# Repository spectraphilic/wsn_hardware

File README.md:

# wsn_hardware
Hardware design for the WSN stations

[Eagle](https://www.autodesk.com/products/eagle/overview) files for sensors and other hardware developed at UiO.

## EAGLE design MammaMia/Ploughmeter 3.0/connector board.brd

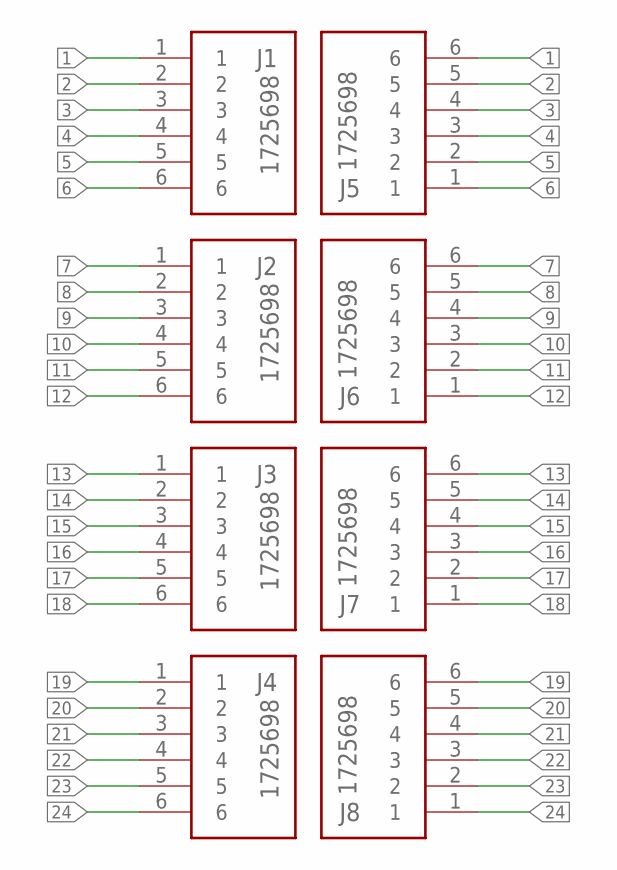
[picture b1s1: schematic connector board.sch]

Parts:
J1, J2, J3, J4, J5, J6, J7, J8: 1725698; SHDR6W90P0X254_1X6_1570X620X85

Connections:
1: J1.1, J5.6
2: J1.2, J5.5
3: J1.3, J5.4
4: J1.4, J5.3
5: J1.5, J5.2
6: J1.6, J5.1
7: J2.1, J6.6
8: J2.2, J6.5
9: J2.3, J6.4
10: J2.4, J6.3
11: J2.5, J6.2
12: J2.6, J6.1
13: J3.1, J7.6
14: J3.2, J7.5
15: J3.3, J7.4
16: J3.4, J7.3
17: J3.5, J7.2
18: J3.6, J7.1
19: J4.1, J8.6
20: J4.2, J8.5
21: J4.3, J8.4
22: J4.4, J8.3
23: J4.5, J8.2
24: J4.6, J8.1

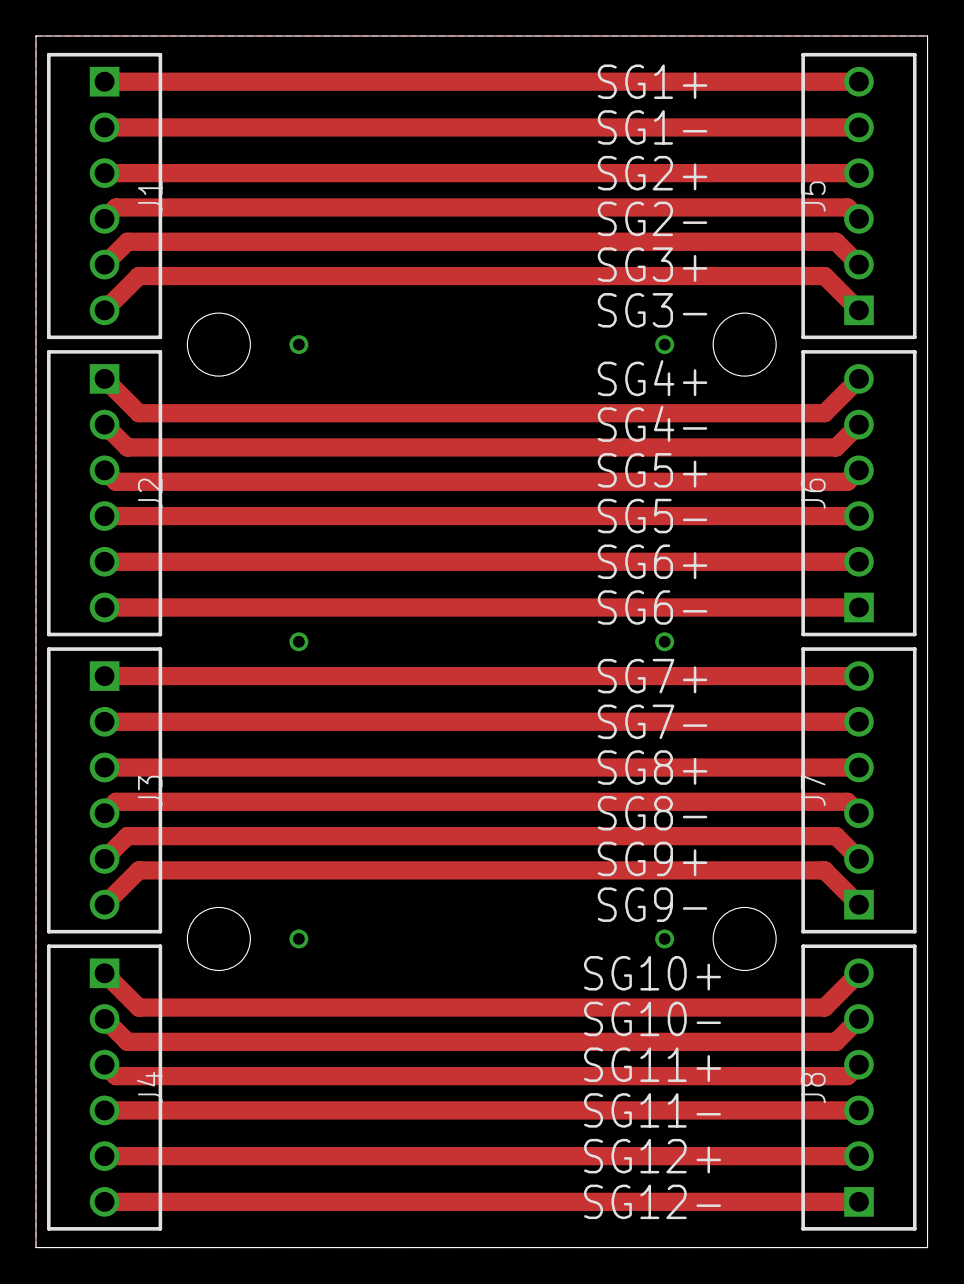
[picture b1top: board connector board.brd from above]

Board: 2 copper layers, 49.5 x 67.3 mm, 8 parts (0 on the bottom side), 24 nets.

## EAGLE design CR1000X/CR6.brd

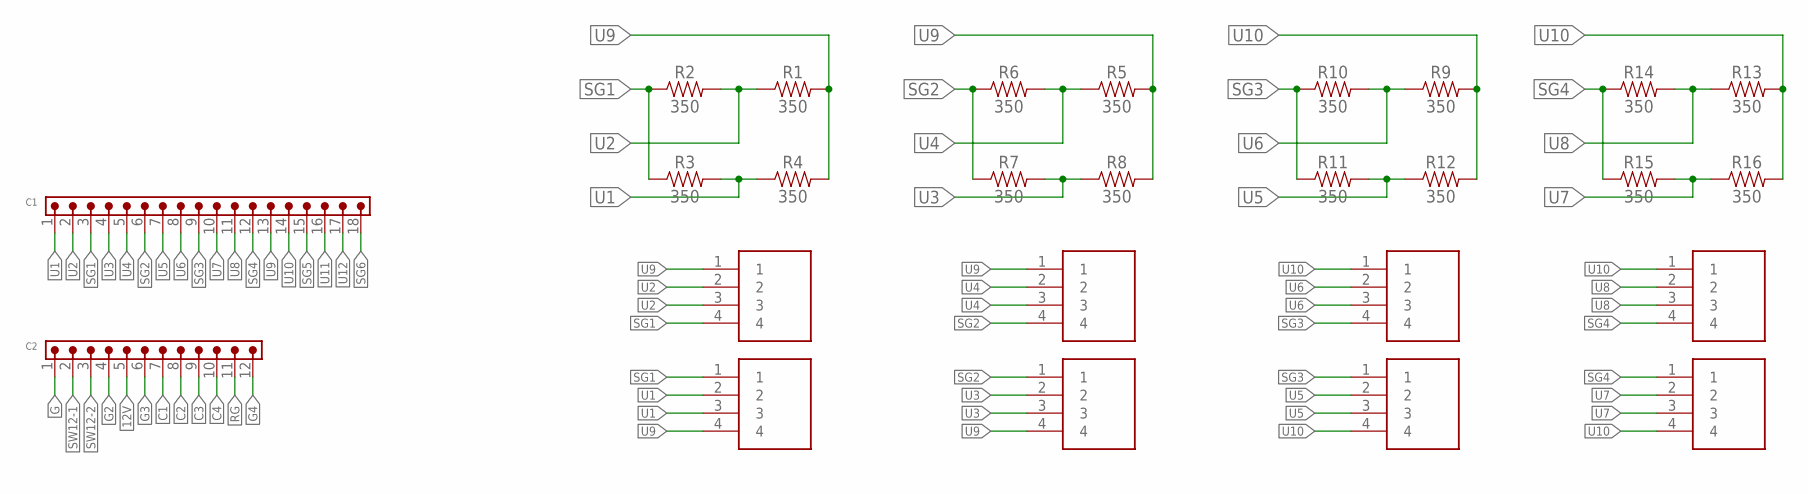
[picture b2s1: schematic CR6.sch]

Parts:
C1: WURTH_CONNECTORS_WR-TBL-PLUGGABLE-CONNECTOR_69131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; WURTH_CONNECTORS_WR-TBL-PLUGGABLE-CONNECTOR_691311500018
C2: WURTH_CONNECTORS_WR-TBL-PLUGGABLE-CONNECTOR_69131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; WURTH_CONNECTORS_WR-TBL-PLUGGABLE-CONNECTOR_691311500012
J1, J2, J5, J6, J9, J10, J13, J14: 1725672; 1725672-4-2.54
R1, R2, R3, R4, R5, R6, R7, R8, R9, R10, R11, R12, R13, R14, R15, R16: 350; AXIAL-0.3

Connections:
12V: C2.5
C1: C2.7
C2: C2.8
C3: C2.9
C4: C2.10
G: C2.1
G2: C2.4
G3: C2.6
G4: C2.12
RG: C2.11
SG1: C1.3, J1.4, J2.1, R2.P$1 (1), R3.P$1 (1)
SG2: C1.6, J5.4, J6.1, R6.P$1 (1), R7.P$1 (1)
SG3: C1.9, J9.4, J10.1, R10.P$1 (1), R11.P$1 (1)
SG4: C1.12, J13.4, J14.1, R14.P$1 (1), R15.P$1 (1)
SG5: C1.15
SG6: C1.18
SW12-1: C2.2
SW12-2: C2.3
U1: C1.1, J2.2, J2.3, R3.P$2 (2), R4.P$1 (1)
U2: C1.2, J1.2, J1.3, R1.P$1 (1), R2.P$2 (2)
U3: C1.4, J6.2, J6.3, R7.P$2 (2), R8.P$1 (1)
U4: C1.5, J5.2, J5.3, R5.P$1 (1), R6.P$2 (2)
U5: C1.7, J10.2, J10.3, R11.P$2 (2), R12.P$1 (1)
U6: C1.8, J9.2, J9.3, R9.P$1 (1), R10.P$2 (2)
U7: C1.10, J14.2, J14.3, R15.P$2 (2), R16.P$1 (1)
U8: C1.11, J13.2, J13.3, R13.P$1 (1), R14.P$2 (2)
U9: C1.13, J1.1, J2.4, J5.1, J6.4, R1.P$2 (2), R4.P$2 (2), R5.P$2 (2), R8.P$2 (2)
U10: C1.14, J9.1, J10.4, J13.1, J14.4, R9.P$2 (2), R12.P$2 (2), R13.P$2 (2), R16.P$2 (2)
U11: C1.16
U12: C1.17

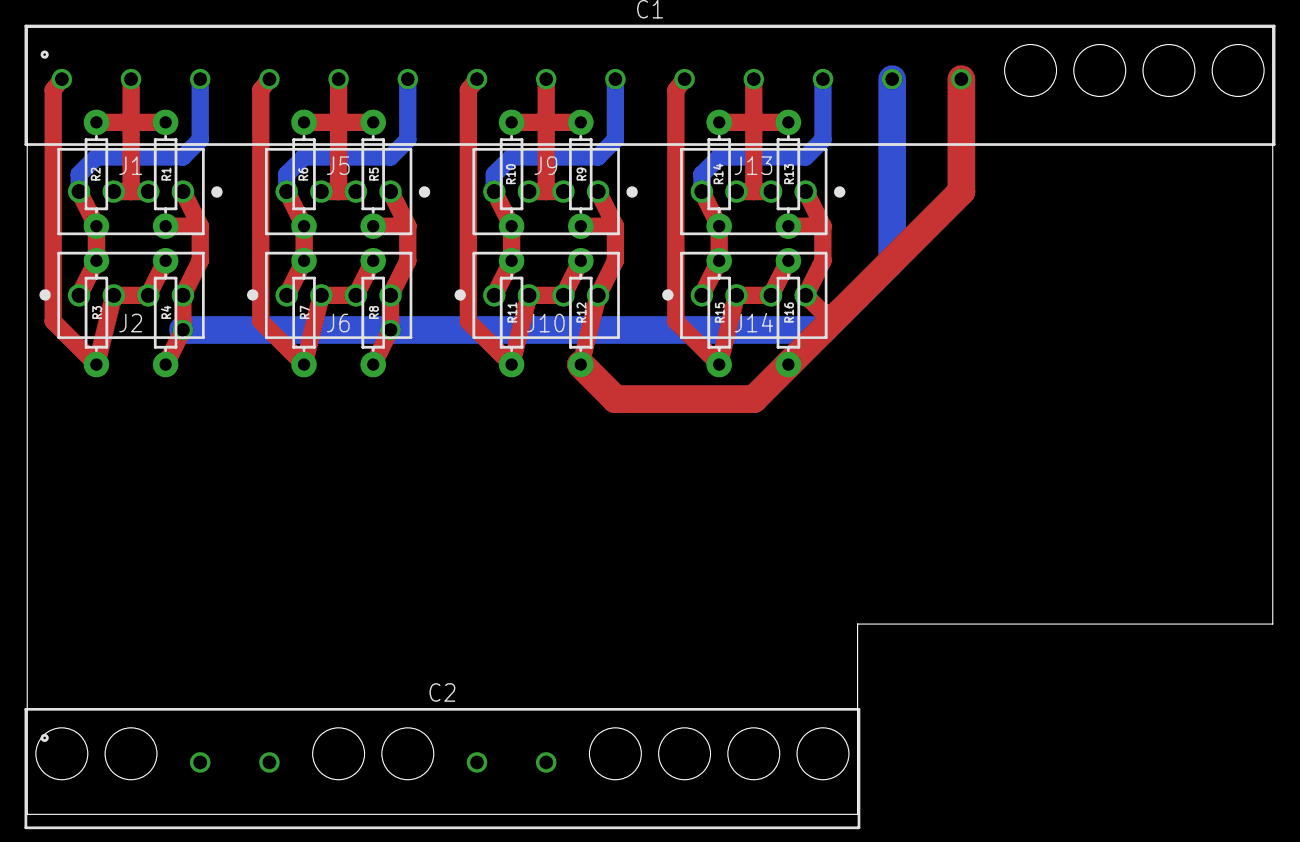
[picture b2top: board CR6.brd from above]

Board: 2 copper layers, 91.4 x 57.8 mm, 26 parts (0 on the bottom side), 14 nets.

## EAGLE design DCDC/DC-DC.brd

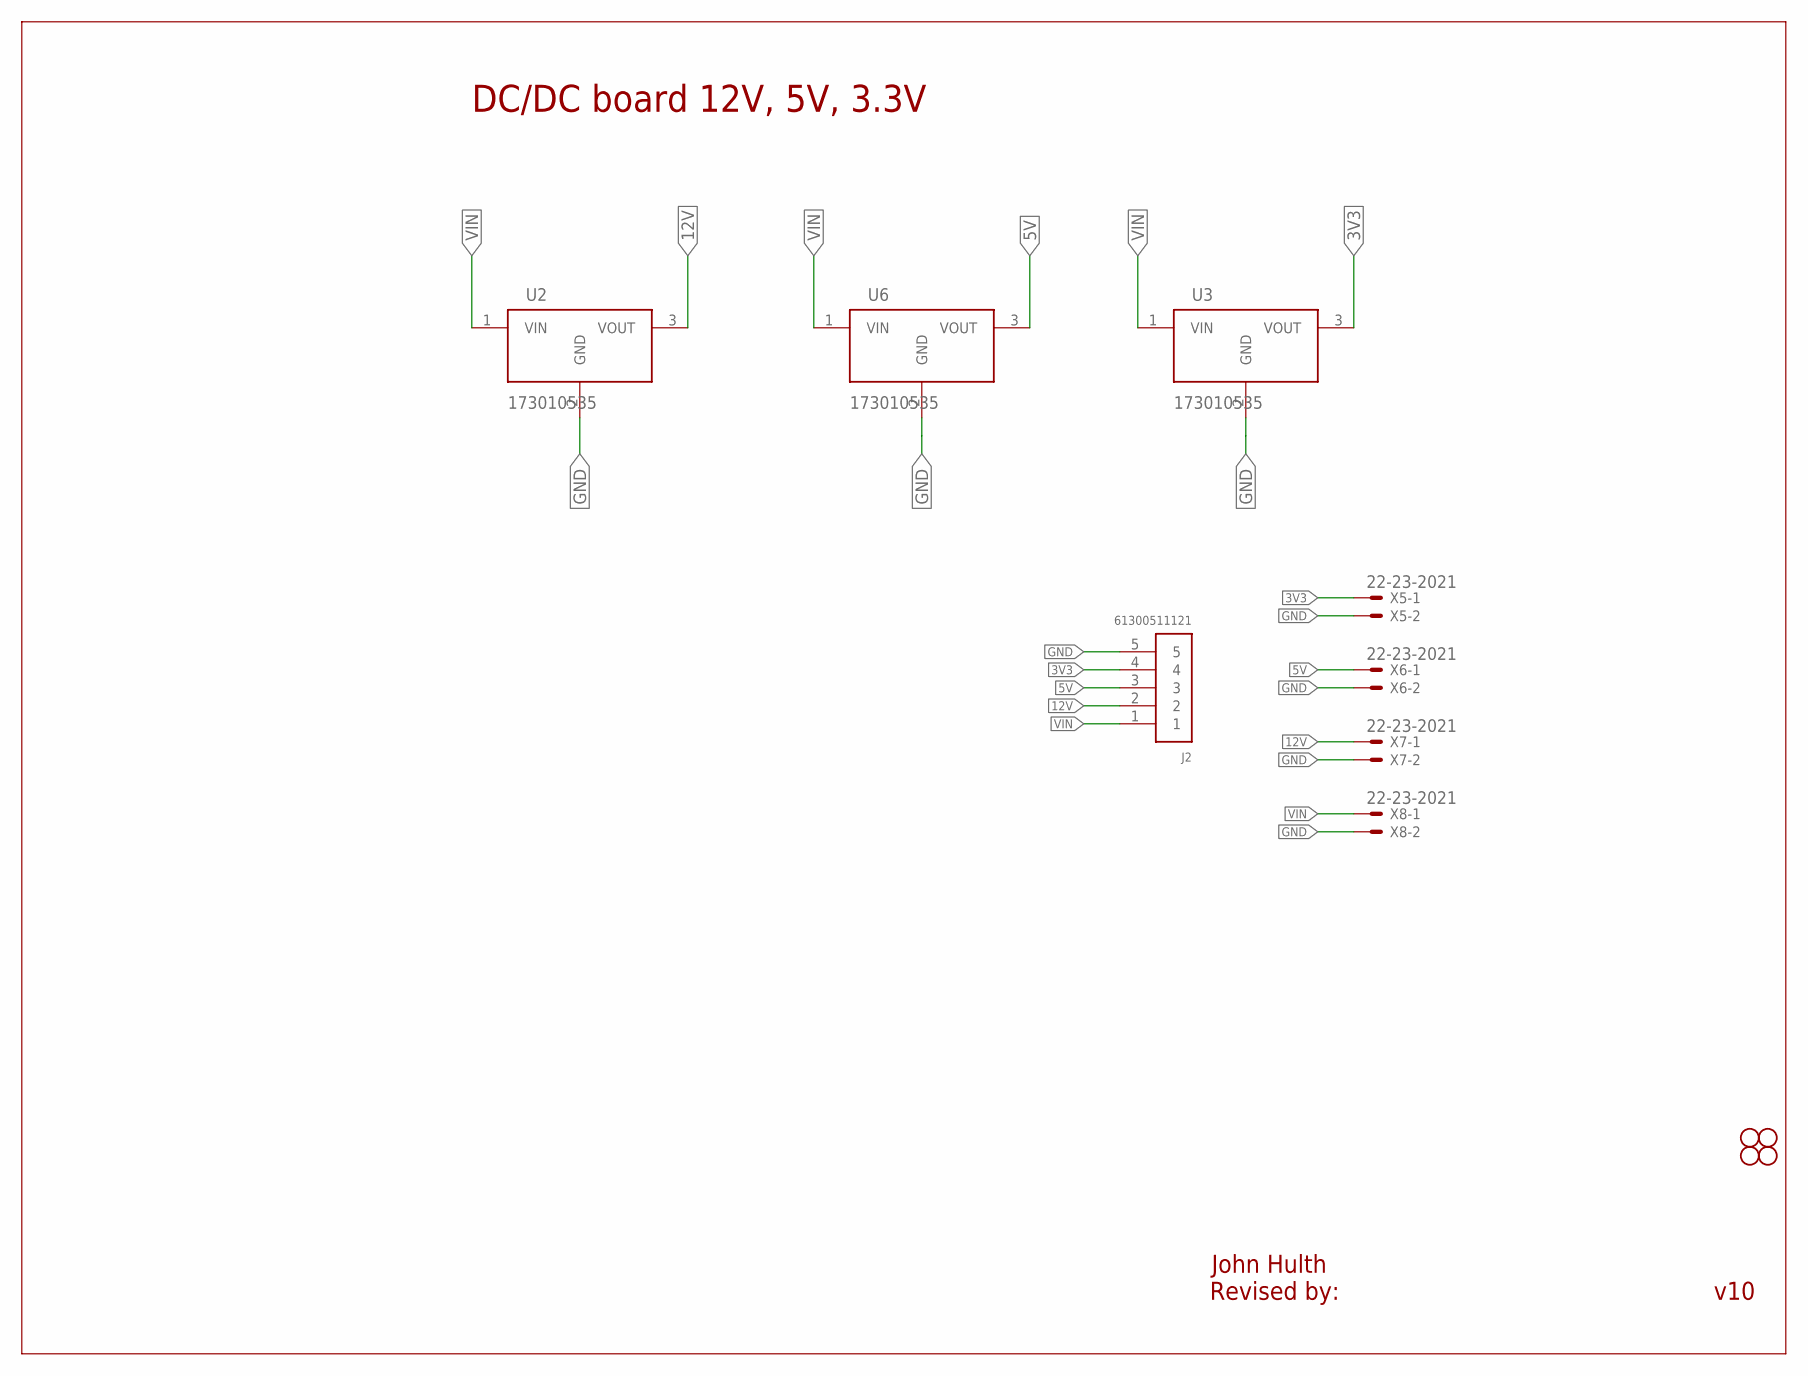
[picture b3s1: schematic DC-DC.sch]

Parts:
J2: 61300511121
JP1, JP4, JP5, JP6: STAND-OFF
U2, U3, U6: 173010535
X5, X6, X7, X8: 22-23-2021

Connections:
3V3: J2.4, U3.3 (VOUT), X5.1
5V: J2.3, U6.3 (VOUT), X6.1
12V: J2.2, U2.3 (VOUT), X7.1
GND: J2.5, U2.2 (GND), U3.2 (GND), U6.2 (GND), X5.2, X6.2, X7.2, X8.2
VIN: J2.1, U2.1 (VIN), U3.1 (VIN), U6.1 (VIN), X8.1

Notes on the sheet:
DC/DC board 12V, 5V, 3.3V
John Hulth
v10
Revised by:

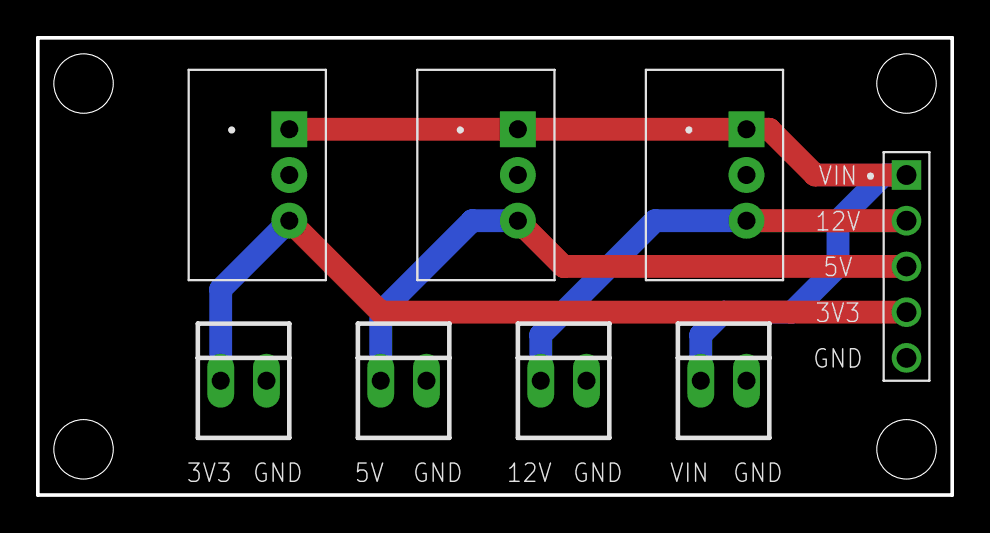
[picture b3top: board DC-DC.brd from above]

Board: 2 copper layers, 50.8 x 25.4 mm, 13 parts (1 on the bottom side), 5 nets.

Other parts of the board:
U$1: UIO-LOGO-BL

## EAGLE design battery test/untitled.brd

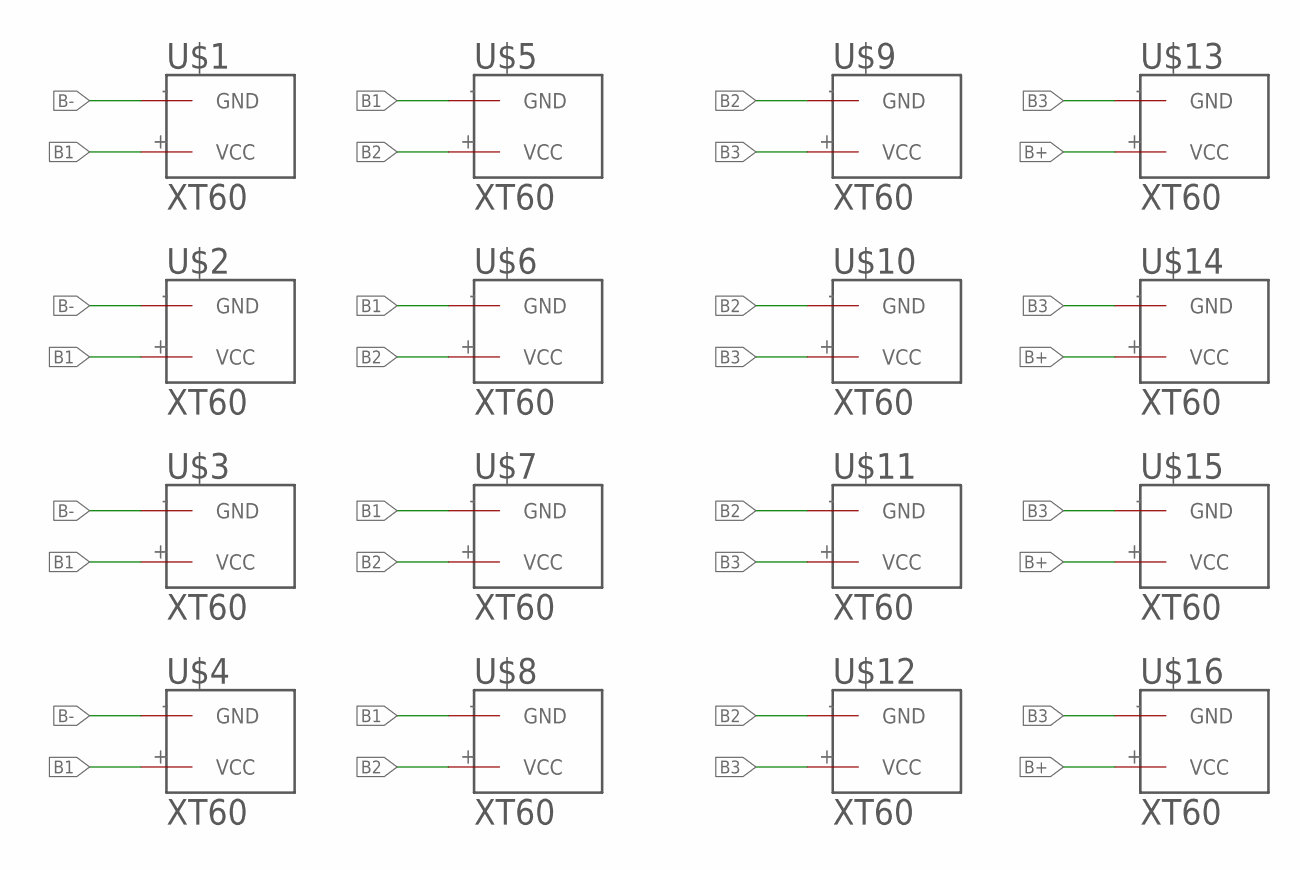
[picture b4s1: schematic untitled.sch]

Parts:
U$1, U$2, U$3, U$4, U$5, U$6, U$7, U$8, U$9, U$10, U$11, U$12, U$13, U$14, U$15, U$16: XT60

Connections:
B1: U$1.+ (VCC), U$2.+ (VCC), U$3.+ (VCC), U$4.+ (VCC), U$5.- (GND), U$6.- (GND), U$7.- (GND), U$8.- (GND)
B2: U$5.+ (VCC), U$6.+ (VCC), U$7.+ (VCC), U$8.+ (VCC), U$9.- (GND), U$10.- (GND), U$11.- (GND), U$12.- (GND)
B3: U$9.+ (VCC), U$10.+ (VCC), U$11.+ (VCC), U$12.+ (VCC), U$13.- (GND), U$14.- (GND), U$15.- (GND), U$16.- (GND)
B+: U$13.+ (VCC), U$14.+ (VCC), U$15.+ (VCC), U$16.+ (VCC)
B-: U$1.- (GND), U$2.- (GND), U$3.- (GND), U$4.- (GND)

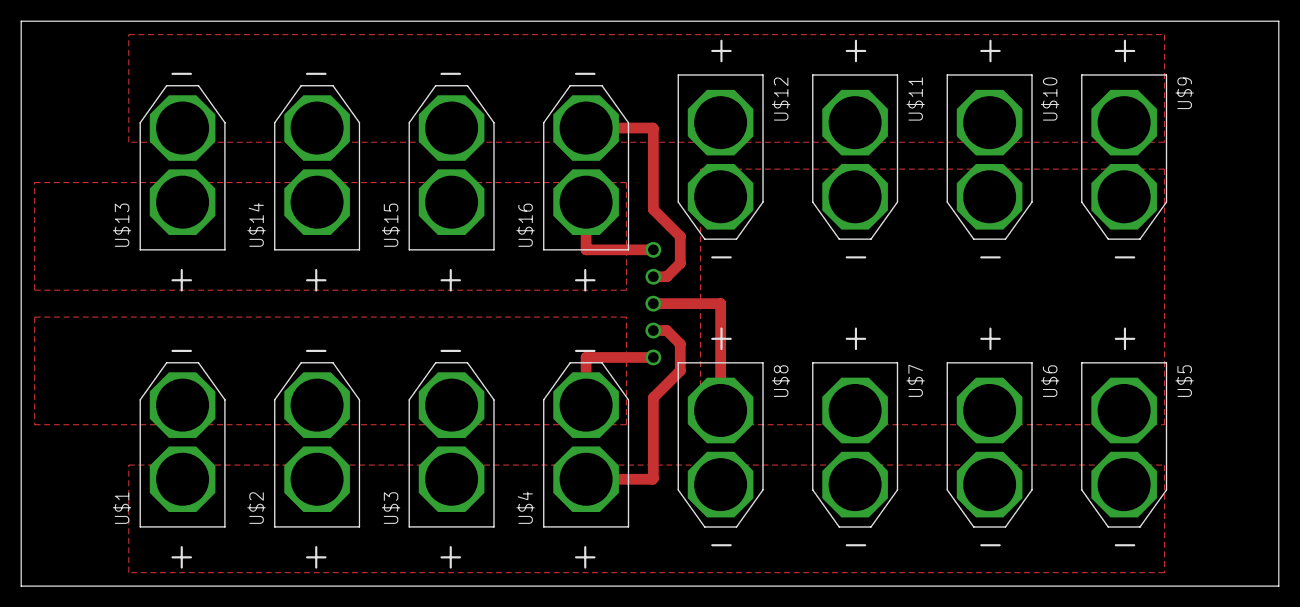
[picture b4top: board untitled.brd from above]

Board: 2 copper layers, 118.7 x 53.3 mm, 16 parts (0 on the bottom side), 5 nets.

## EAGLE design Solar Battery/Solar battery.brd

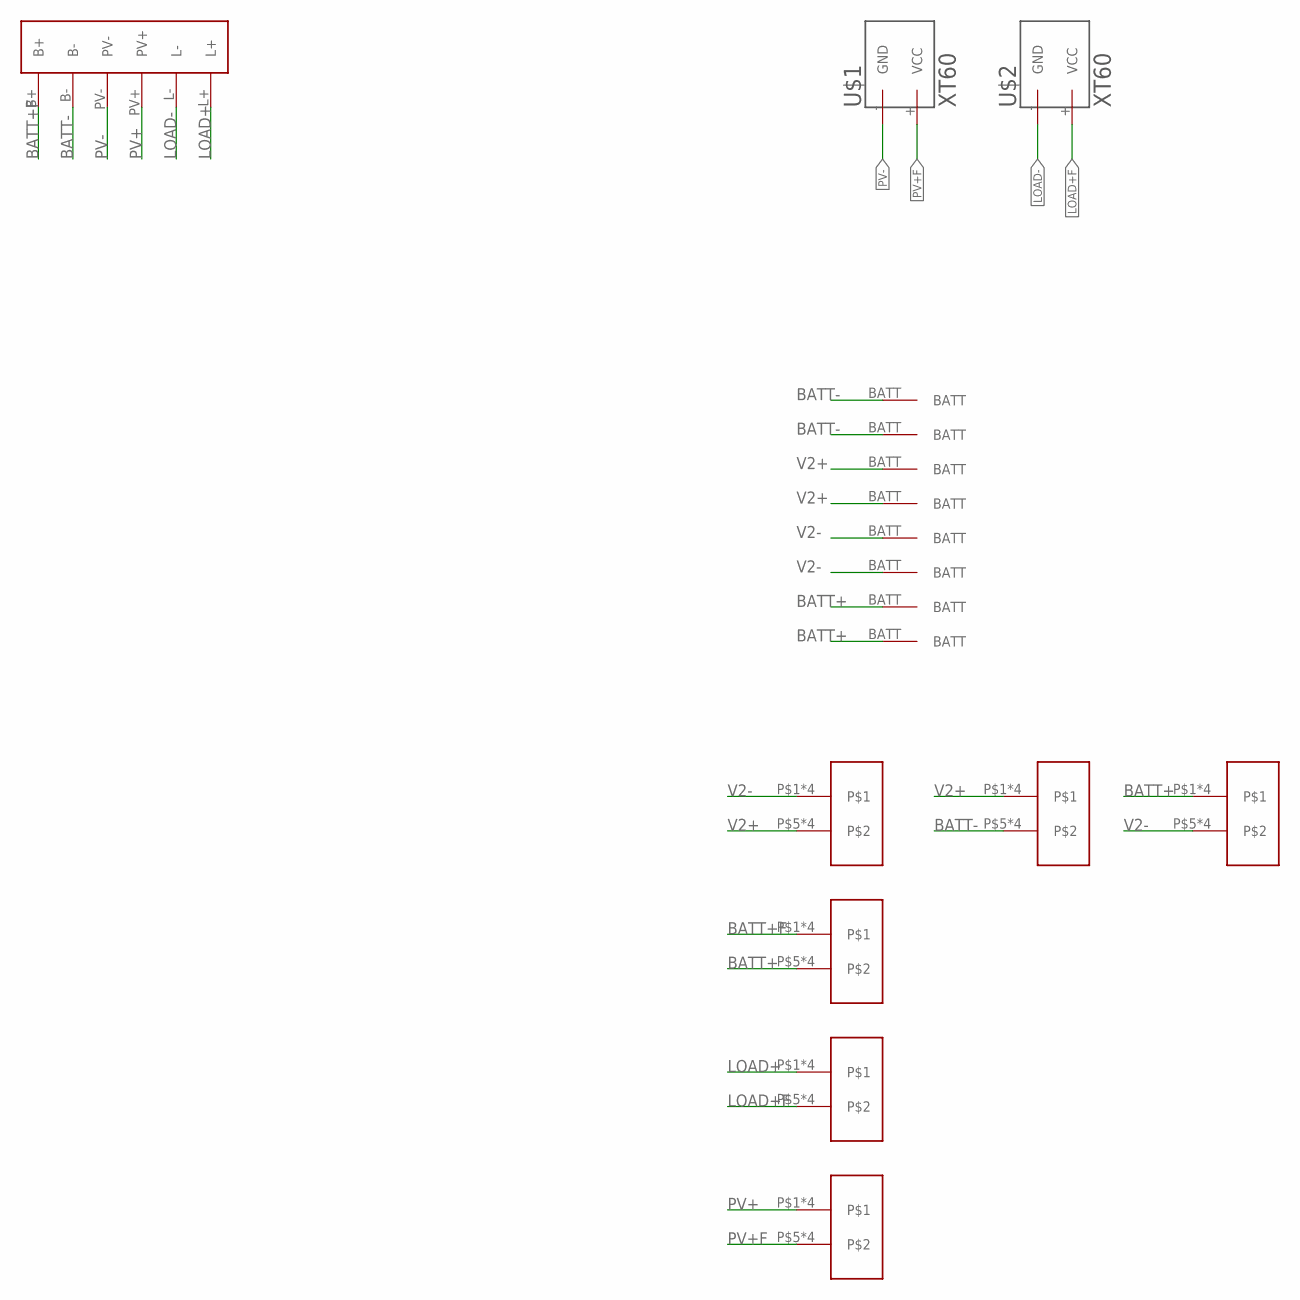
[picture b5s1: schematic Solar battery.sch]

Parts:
U$1, U$2: XT60
U$3, U$4, U$5, U$6, U$7, U$8, U$9, U$10: C40_40135
U$11, U$12, U$13, U$14, U$15, U$16: FUSEHOLDER_178.6164
U$17: SMARTSOLAR_75/15

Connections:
BATT+: U$9.BATT, U$10.BATT, U$12.P$5, U$12.P$6, U$12.P$7, U$12.P$8, U$16.P$1, U$16.P$2, U$16.P$3, U$16.P$4
BATT+F: U$12.P$1, U$12.P$2, U$12.P$3, U$12.P$4, U$17.B+
BATT-: U$3.BATT, U$4.BATT, U$15.P$5, U$15.P$6, U$15.P$7, U$15.P$8, U$17.B-
LOAD+: U$13.P$1, U$13.P$2, U$13.P$3, U$13.P$4, U$17.L+
LOAD+F: U$2.+ (VCC), U$13.P$5, U$13.P$6, U$13.P$7, U$13.P$8
LOAD-: U$2.- (GND), U$17.L-
PV+: U$14.P$1, U$14.P$2, U$14.P$3, U$14.P$4, U$17.PV+
PV+F: U$1.+ (VCC), U$14.P$5, U$14.P$6, U$14.P$7, U$14.P$8
PV-: U$1.- (GND), U$17.PV-
V2+: U$5.BATT, U$6.BATT, U$11.P$5, U$11.P$6, U$11.P$7, U$11.P$8, U$15.P$1, U$15.P$2, U$15.P$3, U$15.P$4
V2-: U$7.BATT, U$8.BATT, U$11.P$1, U$11.P$2, U$11.P$3, U$11.P$4, U$16.P$5, U$16.P$6, U$16.P$7, U$16.P$8

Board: 2 copper layers, 18 parts (3 on the bottom side), 11 nets, no tracks yet.

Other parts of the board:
U$18: UIO-LOGO-BL

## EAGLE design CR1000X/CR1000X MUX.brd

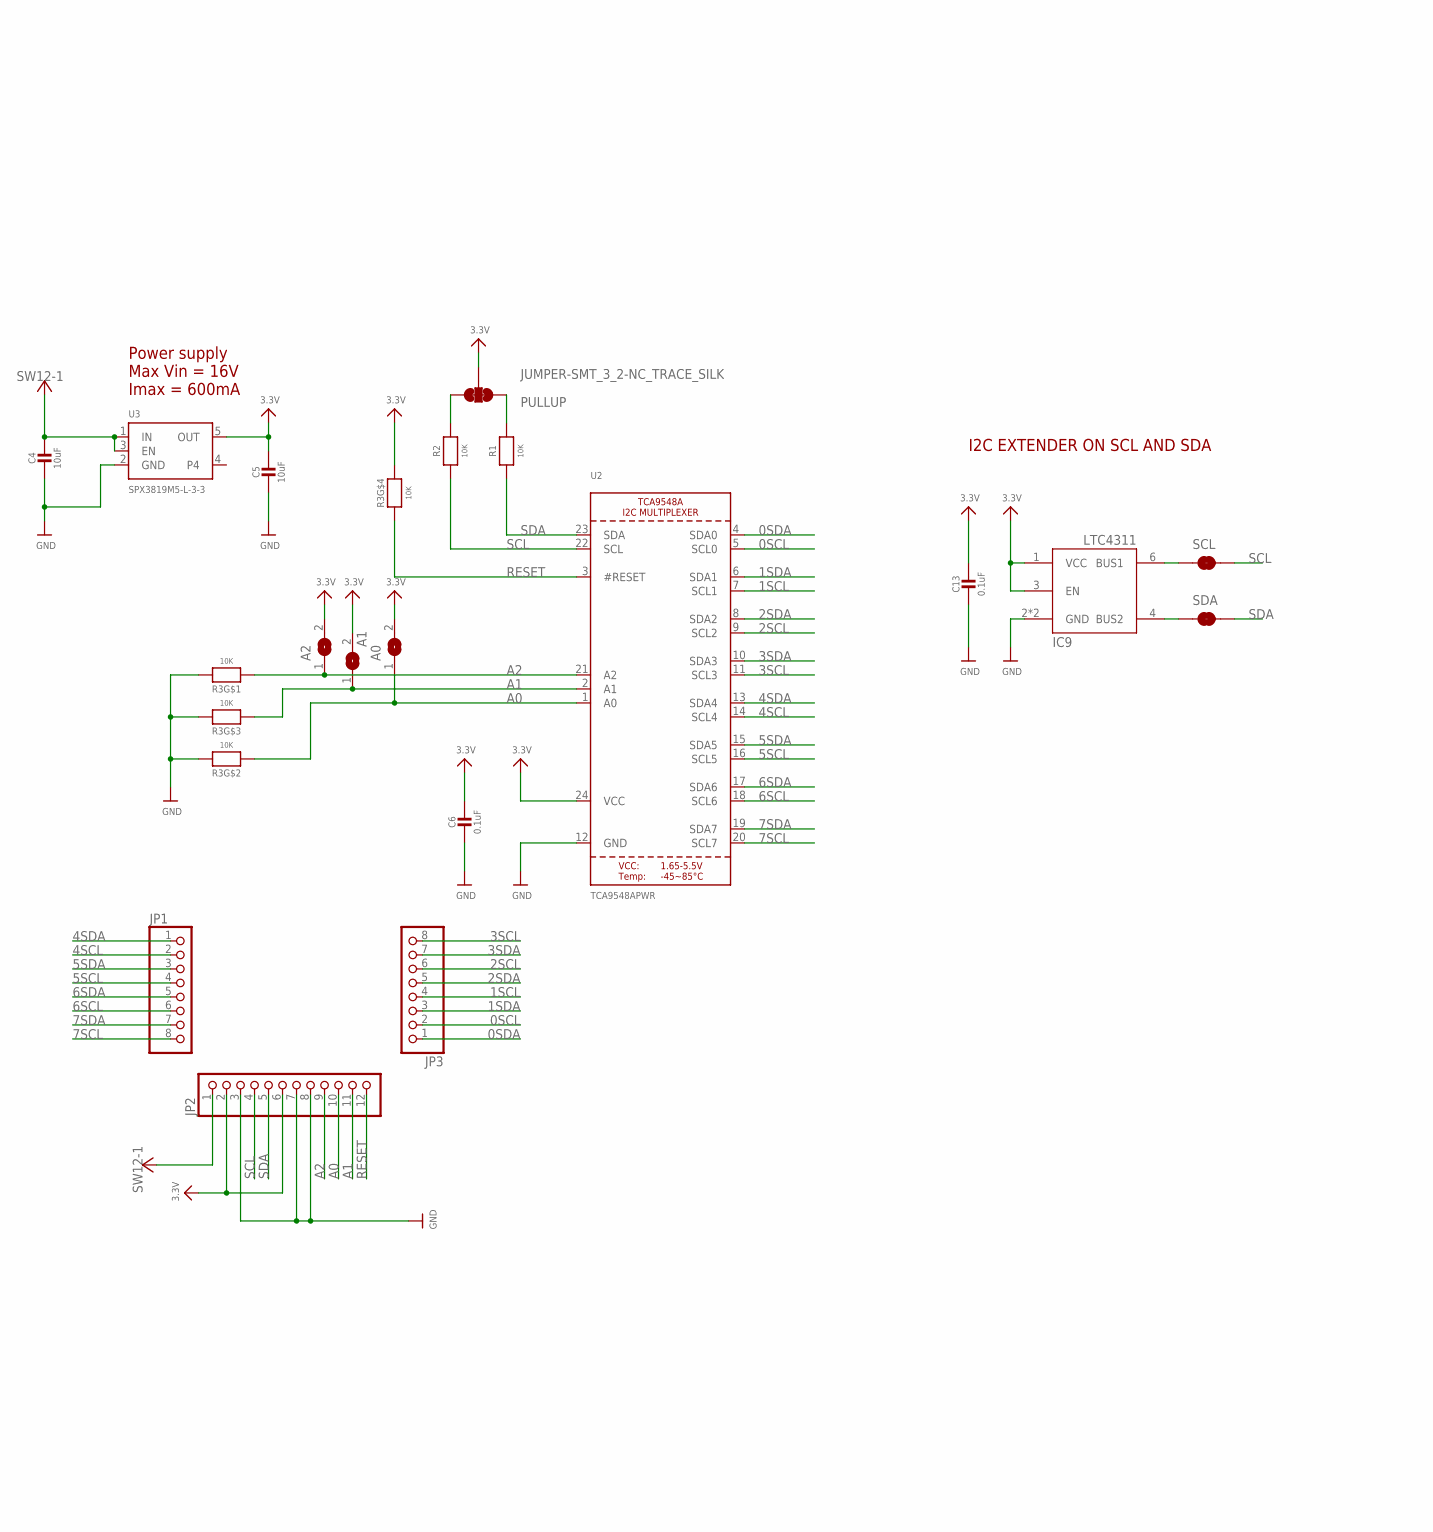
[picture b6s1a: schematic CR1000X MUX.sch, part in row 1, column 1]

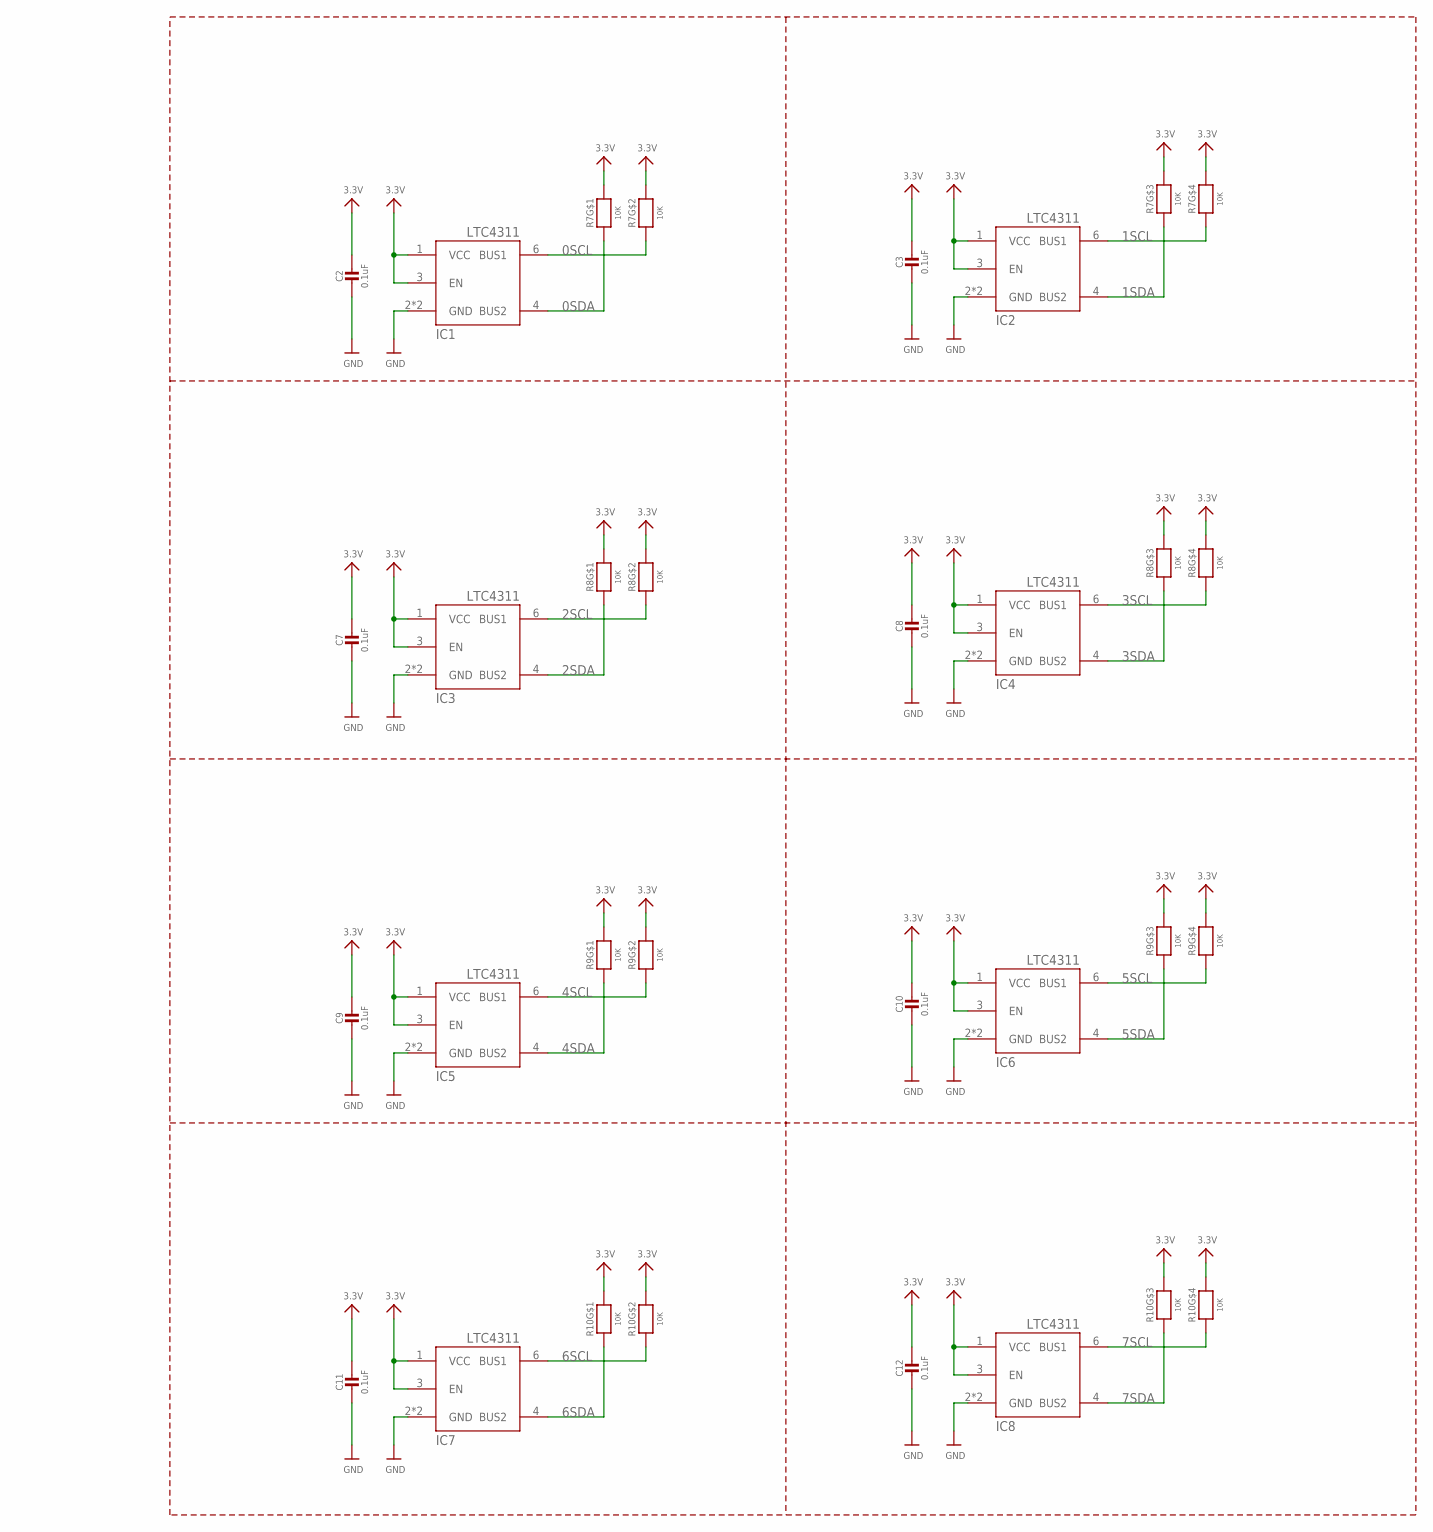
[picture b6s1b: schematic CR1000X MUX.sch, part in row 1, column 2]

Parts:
A0, A1, A2: SOLDERJUMPER; SOLDERJUMPER_ARROW_NOPASTE
C2, C3, C6, C7, C8, C9, C10, C11, C12, C13: 0.1uF; 0603-NO
C4, C5: 10uF; 0805-NO
IC1, IC2, IC3, IC4, IC5, IC6, IC7, IC8, IC9: LTC4311_SC70; SC70-6L
JP1, JP3: PINHD-1X8BIG; 1X08-BIG
JP2: HEADER-1X12; 1X12_ROUND
PULLUP: JUMPER-SMT_3_2-NC_TRACE_SILK; SMT-JUMPER_3_2-NC_TRACE_SILK
R1, R2: 10K; 0805-NO@1
R3, R7, R8, R9, R10: 10K; RESPACK_4X0603
SCL: JUMPER-SMT_2_NC_TRACE_SILK; SMT-JUMPER_2_NC_TRACE_SILK
SDA: JUMPER-SMT_2_NC_TRACE_SILK; SMT-JUMPER_2_NC_TRACE_SILK
U2: TCA9548APWR; TSSOP24
U3: SPX3819M5-L-3-3; SOT23-5

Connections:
0SCL: IC1.6 (BUS1), JP3.2, R7.7 (2), U2.5 (SCL0)
0SDA: IC1.4 (BUS2), JP3.1, R7.8 (2), U2.4 (SDA0)
1SCL: IC2.6 (BUS1), JP3.4, R7.5 (2), U2.7 (SCL1)
1SDA: IC2.4 (BUS2), JP3.3, R7.6 (2), U2.6 (SDA1)
2SCL: IC3.6 (BUS1), JP3.6, R8.7 (2), U2.9 (SCL2)
2SDA: IC3.4 (BUS2), JP3.5, R8.8 (2), U2.8 (SDA2)
3.3V: A0.2, A1.2, A2.2, C2.1, C3.1, C5.1, C6.1, C7.1, C8.1, C9.1, C10.1, C11.1, C12.1, C13.1, IC1.1 (VCC), IC1.3 (EN), IC2.1 (VCC), IC2.3 (EN), IC3.1 (VCC), IC3.3 (EN), IC4.1 (VCC), IC4.3 (EN), IC5.1 (VCC), IC5.3 (EN), IC6.1 (VCC), IC6.3 (EN), IC7.1 (VCC), IC7.3 (EN), IC8.1 (VCC), IC8.3 (EN), IC9.1 (VCC), IC9.3 (EN), JP2.2, JP2.6, PULLUP.2, R3.4 (1), R7.1, R7.2 (1), R7.3 (1), R7.4 (1), R8.1, R8.2 (1), R8.3 (1), R8.4 (1), R9.1, R9.2 (1), R9.3 (1), R9.4 (1), R10.1, R10.2 (1), R10.3 (1), R10.4 (1), U2.24 (VCC), U3.5 (OUT)
3SCL: IC4.6 (BUS1), JP3.8, R8.5 (2), U2.11 (SCL3)
3SDA: IC4.4 (BUS2), JP3.7, R8.6 (2), U2.10 (SDA3)
4SCL: IC5.6 (BUS1), JP1.2, R9.7 (2), U2.14 (SCL4)
4SDA: IC5.4 (BUS2), JP1.1, R9.8 (2), U2.13 (SDA4)
5SCL: IC6.6 (BUS1), JP1.4, R9.5 (2), U2.16 (SCL5)
5SDA: IC6.4 (BUS2), JP1.3, R9.6 (2), U2.15 (SDA5)
6SCL: IC7.6 (BUS1), JP1.6, R10.7 (2), U2.18 (SCL6)
6SDA: IC7.4 (BUS2), JP1.5, R10.8 (2), U2.17 (SDA6)
7SCL: IC8.6 (BUS1), JP1.8, R10.5 (2), U2.20 (SCL7)
7SDA: IC8.4 (BUS2), JP1.7, R10.6 (2), U2.19 (SDA7)
A0: A0.1, JP2.10, R3.7 (2), U2.1 (A0)
A1: A1.1, JP2.11, R3.6 (2), U2.2 (A1)
A2: A2.1, JP2.9, R3.8 (2), U2.21 (A2)
GND: C2.2, C3.2, C4.2, C5.2, C6.2, C7.2, C8.2, C9.2, C10.2, C11.2, C12.2, C13.2, IC1.2 (GND), IC1.5 (GND), IC2.2 (GND), IC2.5 (GND), IC3.2 (GND), IC3.5 (GND), IC4.2 (GND), IC4.5 (GND), IC5.2 (GND), IC5.5 (GND), IC6.2 (GND), IC6.5 (GND), IC7.2 (GND), IC7.5 (GND), IC8.2 (GND), IC8.5 (GND), IC9.2 (GND), IC9.5 (GND), JP2.3, JP2.7, JP2.8, R3.1, R3.2 (1), R3.3 (1), U2.12 (GND), U3.2 (GND)
unnamed: PULLUP.3, R2.2
unnamed: PULLUP.1, R1.2
unnamed: IC9.6 (BUS1), SCL.1
unnamed: IC9.4 (BUS2), SDA.1
RESET: JP2.12, R3.5 (2), U2.3 (#RESET)
SCL: JP2.4, R2.1, SCL.2, U2.22 (SCL)
SDA: JP2.5, R1.1, SDA.2, U2.23 (SDA)
SW12-1: C4.1, JP2.1, U3.1 (IN), U3.3 (EN)

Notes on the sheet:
Power supply Max Vin = 16V Imax = 600mA
I2C EXTENDER ON SCL AND SDA

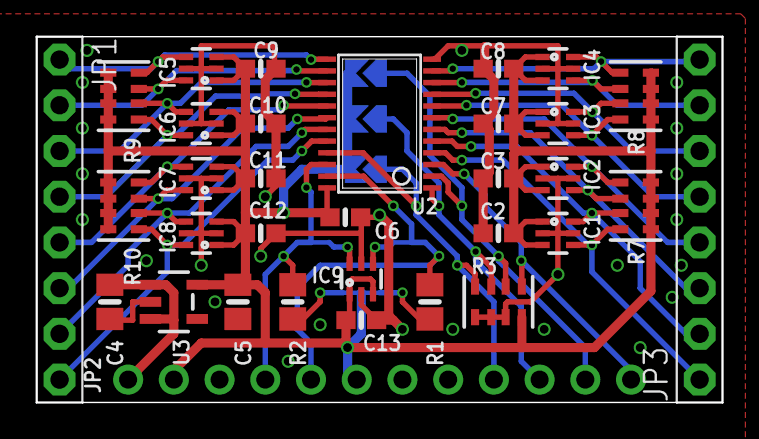
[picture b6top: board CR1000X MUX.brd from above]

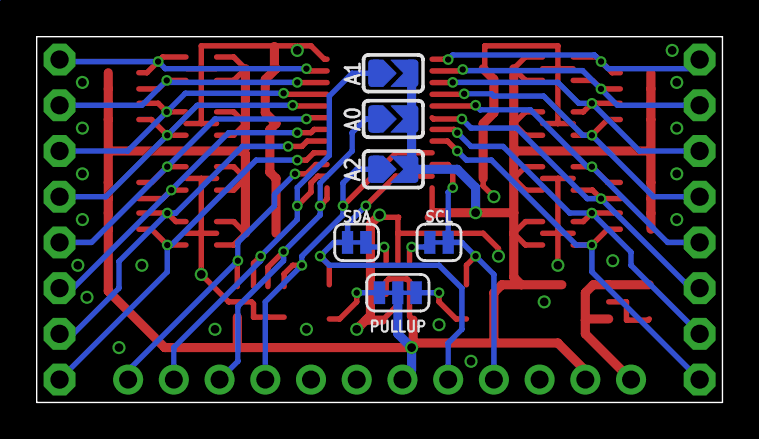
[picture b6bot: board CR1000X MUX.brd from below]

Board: 2 copper layers, 38.1 x 20.3 mm, 39 parts (6 on the bottom side), 29 nets.

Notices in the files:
DCDC/DC-DC.brd:
(C) 2020
Solar Battery/Solar battery.brd:
(C) 2024
parts and their libraries:
microbuilder: This work is placed in the public domain, and may be freely used for commercial and non-commercial work with the following conditions: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
SparkFun-Jumpers: Licensing: Creative Commons ShareAlike 4.0 International - https://creativecommons.org/licenses/by-sa/4.0
